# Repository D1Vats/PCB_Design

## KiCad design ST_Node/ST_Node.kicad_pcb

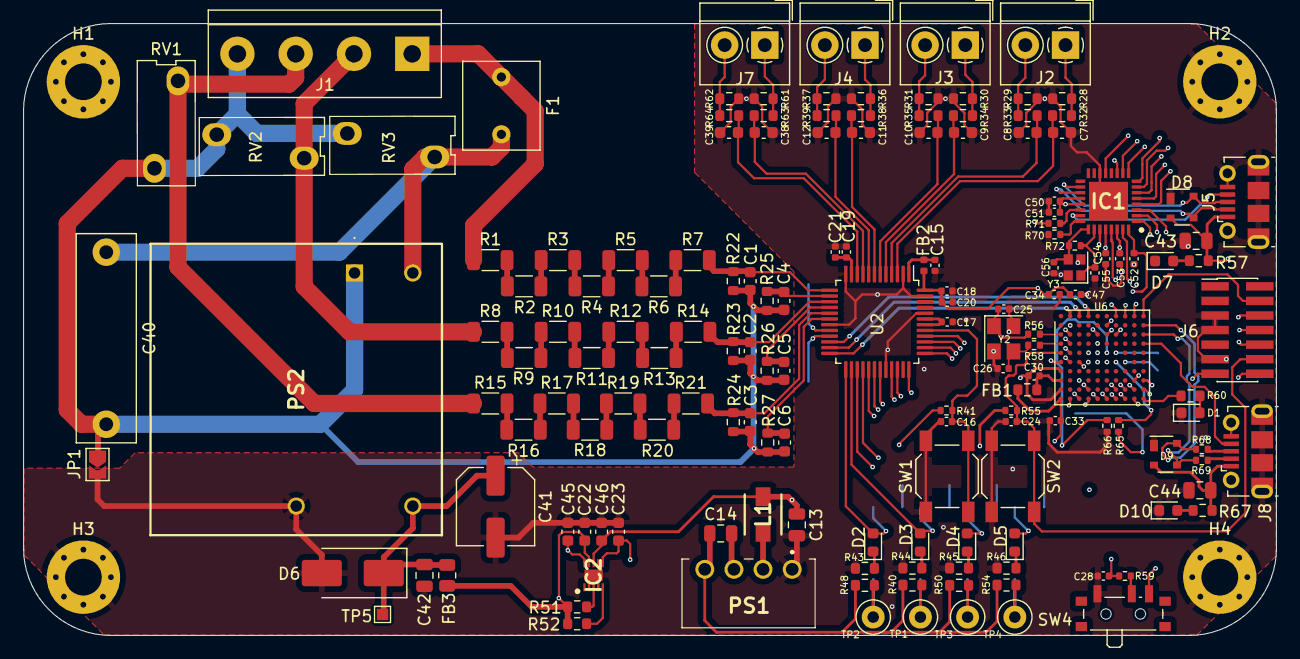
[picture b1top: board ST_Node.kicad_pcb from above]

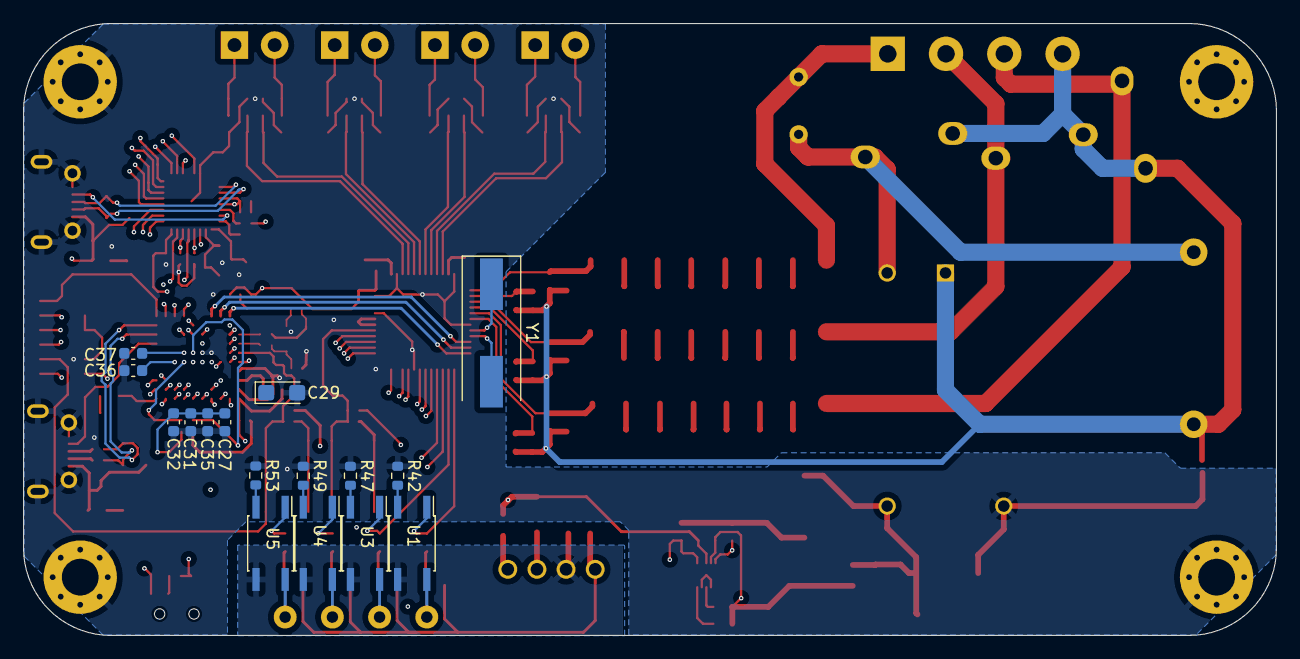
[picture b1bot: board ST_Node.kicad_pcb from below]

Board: 6 copper layers, 109.2 x 53.3 mm, 178 parts (16 on the bottom side), 138 nets.

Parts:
C1, C2, C3, C4, C5, C6, C7, C8, C9, C10, C11, C12, C38, C39: 18nf; C_0603_1608Metric
C13: 4.7uf/16V; C_0805_2012Metric
C14: 10uf/16V; C_0805_2012Metric
C15, C16, C18, C19: 0.1uf; C_0402_1005Metric
C17, C20, C21: 10uf; C_0402_1005Metric
C22, C23: 1uf; C_0603_1608Metric
C24, C28, C33, C34, C47, C50, C51, C52, C53, C54: 100nf; C_0402_1005Metric
C25, C26, C55, C56: 12pf; C_0402_1005Metric
C27, C31, C32: 100nf; C_0603_1608Metric
C29: 1uf; CP_EIA-3216-18_Kemet-A
C30: 10nf; C_0402_1005Metric
C35: 4.7uf; C_0603_1608Metric
C36, C37: 2.2uf; C_0603_1608Metric
C40: 0.1uf/305V; C_Rect_L18.0mm_W5.0mm_P15.00mm_FKS3_FKP3
C41: 100uf/25V; CP_Elec_6.3x7.7
C42: 1uf/50V; C_0805_2012Metric
C43, C44: 4.7nf; C_0805_2012Metric
C45, C46: 10uf; C_0603_1608Metric
D1, D7, D10: Green_LED; LED_0603_1608Metric
D2, D3, D4, D5: LED; LED_0603_1608Metric
D6: SM6T12A; D_SMB_Handsoldering
D8, D9: SP0503BAHT; SOT-143
F1: 2A/300V; C_Rect_L7.5mm_W6.5mm_P5.00mm
FB1: 600@100Mhz; R_0603_1608Metric
FB2: FerriteBead_Small; Fuse_0402_1005Metric
FB3: 120R; R_0805_2012Metric
H1, H2, H3, H4: MountingHole_Pad; MountingHole_3.2mm_M3_Pad_Via
IC1: USB3320C-EZK-TR; QFN50P500X500X100-33N-D
IC2: TLV751180330PDSQR; SON40P200X200X80-11N
J1: 3Phase_Input; TerminalBlock_bornier-4_P5.08mm
J2: CT_Coil_1; TerminalBlock_4Ucon_1x02_P3.50mm_Horizontal
J3: CT_Coil_2; TerminalBlock_4Ucon_1x02_P3.50mm_Horizontal
J4, J7: CT_Coil_3; TerminalBlock_4Ucon_1x02_P3.50mm_Horizontal
J5, J8: USB_B_Micro; USB_Micro-B_Molex-105017-0001
J6: Conn_ST_STDC14; PinHeader_2x07_P1.27mm_Vertical_SMD
JP1: Jumper_2_Open; SolderJumper-2_P1.3mm_Open_TrianglePad1.0x1.5mm
L1: SRP3012CC-6R8M; INDPM3532X120N
PS1: B0303S-1WR2; B0303S1WR2
PS2: RACM06E-05SK_277; RACM06E05SK277
R1, R2, R3, R4, R5, R6, R7, R8, R9, R10, R11, R12, R13, R14, R15, R16, R17, R18, R19, R20, R21: 240k; R_1206_3216Metric
R22, R23, R24, R25, R26, R27, R57, R60, R67: 1k; R_0603_1608Metric
R28, R29, R30, R31, R36, R37, R61, R62: 2R7; R_0603_1608Metric
R32, R33, R34, R35, R38, R39, R63, R64: 1K; R_0603_1608Metric
R40, R42, R43, R44, R45, R46, R47, R48, R49, R50, R53, R54: 510R; R_0603_1608Metric
R41, R55, R59, R65, R66: 10k; R_0402_1005Metric
R51, R52: 100k; R_0603_1608Metric
R56, R58: 0R; R_0402_1005Metric
R68, R69: 22E; R_0402_1005Metric
R70: 8.06k; R_0402_1005Metric
R71: 1k; R_0402_1005Metric
R72: 1M; R_0402_1005Metric
RV1, RV2, RV3: S14K350; DIP-2_81_ELL
SW1, SW2: SW_Push; SW_SPST_SKQG_WithStem
SW4: SW_SPDT; SW_SPDT_PCM12
TP1, TP2, TP3, TP4: TestPoint_Probe; TestPoint_Loop_D1.80mm_Drill1.0mm_Beaded
TP5: TestPoint; TestPoint_Pad_1.0x1.0mm
U1, U3, U4, U5: EL817; SO-4_4.4x3.6mm_P2.54mm
U2: M90E36A; LQFP-48_7x7mm_P0.5mm
U6: STM32F746VGHx; TFBGA-100_8x8mm_Layout10x10_P0.8mm
Y1: 16Mhz; Crystal_SMD_HC49-SD
Y2: 16MHz; Crystal_SMD_3225-4Pin_3.2x2.5mm
Y3: 27Mhz; Crystal_SMD_2016-4Pin_2.0x1.6mm

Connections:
3V3_ISO: C14.1, PS1.4 (+VO), R40.2, R48.2, R50.2, R54.2
AC_IN_1/L: F1.1, J1.1, R1.1
AC_IN_2/L: J1.2, R8.1, RV2.1
AC_IN_3/L: J1.3, R15.1, RV1.1
AC_IN/N: C1.2, C2.2, C3.2, C4.2, C5.2, C6.2, C40.2, J1.4, JP1.1 (A), PS2.1 (VAC_IN_(L)), R22.1, R23.1, R24.1, R25.1, R26.1, R27.1, RV1.2, RV2.2, RV3.2
AVDD: C15.1, FB2.2, U2.1 (AVDD)
BOOT_0: C28.1, R59.2, U6.D5 (BOOT0)
BYPASS_REG: R66.1, U6.E6 (BYPASS_REG)
CF1: D2.2 (A), U1.1, U2.25 (CF1)
CF2: D3.2 (A), U2.26 (CF2), U3.1
CF3: D4.2 (A), U2.27 (CF3), U4.1
CF4: D5.2 (A), U2.28 (CF4), U5.1
CS_M90: U2.37 (CS), U6.H9 (PD10)
Coil_1N: J2.2, R29.1, R33.1
Coil_1P: J2.1, R28.2, R32.1
Coil_2N: J3.2, R31.1, R35.1
Coil_2P: J3.1, R30.2, R34.1
Coil_3N: J4.2, R37.1, R39.1
Coil_3P: J4.1, R36.2, R38.1
Coil_4N: J7.2, R62.1, R64.1
Coil_4P: J7.1, R61.2, R63.1
D+: D8.4 (K), IC1.18 (DP), J5.3 (D+)
D-: D8.3 (K), IC1.19 (DM), J5.2 (D-)
DMA_CTRL: U2.36 (DMA_CTRL), U6.J9 (PD9)
Filter_V_IN: C22.1, C23.1, FB3.2, IC2.6 (IN2), IC2.9 (IN1), R51.1, R52.1
GND: C7.2, C8.1, C9.2, C10.1, C11.2, C12.1, C13.2, C15.2, C16.2, C17.2, C18.2, C19.2, C20.2, C21.2, C22.2, C23.2, C24.2, C25.2, C26.2, C27.2, C28.2, C29.2, C30.2, C31.2, C32.2, C33.2, C34.2, C35.2, C36.2, C37.2, C38.2, C39.1, C41.2, C42.2, C43.2, C44.2, C45.2, C46.2, C47.2, C50.2, C51.2, C52.2, C53.2, C54.2, C55.2, C56.2, D1.1 (K), D6.2 (A2), D8.1 (A), D9.1 (A), D10.1 (K), H2.1, H3.1, H4.1, IC1.14 (REFSEL2), IC1.33 (EP), IC2.2 (GND_1), IC2.4 (GND_2), IC2.11 (EP), J5.5 (GND), J5.6 (Shield), J6.5 (GND), J6.7 (GND), J6.11 (GNDDetect), J8.5 (GND), J8.6 (Shield), JP1.2 (B), PS1.1 (GND), PS2.4 (-VOUT), R28.1, R29.2, R30.1, R31.2, R36.1, R37.2, R42.1, R43.1, R44.1, R45.1, R46.1, R47.1, R49.1, R53.1, R61.1, R62.2, R66.2, R70.2, SW1.1, SW2.1, SW4.1 (A), U2.2 (AGND), U2.12 (AGND), U2.19 (DGND), U2.32 (TEST), U2.44 (DGND), U2.47 (DGND), U6.C2 (VSS), U6.E4 (VSS), U6.E5 (VSS), U6.G1 (VSSA), U6.J1 (VSS), Y2.2, Y2.4, Y3.2, Y3.4
GND_ISO: C14.2, PS1.3 (0V), U1.3, U3.3, U4.3, U5.3
I1N: C8.2, R33.2, U2.4 (I1N)
I1P: C7.1, R32.2, U2.3 (I1P)
I2N: C10.2, R35.2, U2.6 (I2N)
I2P: C9.1, R34.2, U2.5 (I2P)
I3N: C12.2, R39.2, U2.8 (I3N)
I3P: C11.1, R38.2, U2.7 (I3P)
I4N: C39.2, R64.2, U2.10 (I4N)
I4P: C38.1, R63.2, U2.9 (I4P)
ID: IC1.23 (ID), J5.4 (ID)
ID_1: J8.4 (ID), U6.D10 (PA10)
IRQ0: U2.30 (IRQ0), U6.K5 (PE9)
IRQ1: U2.31 (IRQ1), U6.K6 (PE13)
NRST: C24.1, J6.12 (~RST), R55.2, SW2.2, U6.E1 (NRST)
unnamed: C25.1, R56.2, Y2.1
unnamed: C26.1, R58.1, Y2.3
unnamed: D1.2 (A), R60.2
unnamed: D2.1 (K), R43.2
unnamed: D3.1 (K), R44.2
unnamed: D4.1 (K), R45.2
unnamed: D5.1 (K), R46.2
unnamed: D7.2 (A), R57.2
unnamed: D10.2 (A), R67.2
unnamed: IC1.24 (RBIAS), R70.1
unnamed: IC1.22 (VBUS), R71.1
unnamed: IC2.3 (EN1), R51.2
unnamed: IC2.5 (EN2), R52.2
unnamed: J8.3 (D+), R68.1
unnamed: J8.2 (D-), R69.1
unnamed: L1.2, PS1.2 (VIN)
unnamed: C40.1, F1.2, PS2.2 (VAC_IN_(N)), RV3.1
unnamed: R1.2, R2.1
unnamed: R2.2, R3.1
unnamed: R3.2, R4.1
unnamed: R4.2, R5.1
unnamed: R5.2, R6.1
unnamed: R6.2, R7.1
unnamed: R8.2, R9.1
unnamed: R9.2, R10.1
unnamed: R10.2, R11.1
unnamed: R11.2, R12.1
unnamed: R12.2, R13.1
unnamed: R13.2, R14.1
unnamed: R15.2, R16.1
unnamed: R16.2, R17.1
unnamed: R17.2, R18.1
unnamed: R18.2, R19.1
unnamed: R19.2, R20.1
unnamed: R20.2, R21.1
unnamed: R40.1, TP1.1, U3.4
unnamed: R42.2, U1.2
unnamed: R47.2, U3.2
unnamed: R48.1, TP2.1, U1.4
unnamed: R49.2, U4.2
unnamed: R50.1, TP3.1, U4.4
unnamed: R53.2, U5.2
unnamed: R54.1, TP4.1, U5.4
unnamed: R59.1, SW4.2 (B)
unnamed: C36.1, U6.F8 (VCAP_1)
unnamed: C37.1, U6.E7 (VCAP_2)
OSCI: U2.20 (OSCI), Y1.1
OSCO: U2.21 (OSCO), Y1.2
OSC_IN: R56.1, U6.C1 (PH0)
OSC_OUT: R58.2, U6.D1 (PH1)
PDR_ON: R65.2, U6.F7 (PDR_ON)
PM0: U2.33 (PM0), U6.K9 (PD8)
PM1: U2.34 (PM1), U6.J10 (PD13)
REFCLK: C55.1, IC1.26 (REFCLK), R72.1, Y3.1
Reset_M90: C16.1, R41.2, SW1.2, U2.41 (RESET)
SCLK_M90: U2.38 (SCLK), U6.C7 (PD3)
SDI_M90: U2.40 (SDI), U6.F2 (PC1)
SDO_M90: U2.39 (SDO), U6.H10 (PB14)
SYS_JTDI: J6.10 (JTDI/NC), U6.A8 (PA15)
SYS_SWCLK: J6.6 (JCLK/SWCLK), U6.A9 (PA14)
SYS_SWDIO: J6.4 (JTMS/SWDIO), U6.A10 (PA13)
SYS_SWO: J6.8 (JTDO/SWO), U6.A7 (PB3)
Test_LED: R60.1, U6.K10 (PD12)
USART2_RX: J6.13 (VCP_RX), U6.C6 (PD6)
USART2_TX: J6.14 (VCP_TX), U6.B6 (PD5)
USB3320_CK: IC1.1 (CLKOUT), U6.H3 (PA5)
USB3320_DIR: IC1.31 (DIR), U6.E2 (PC2)
USB3320_NXT: IC1.2 (NXT), U6.F3 (PC3)
USB3320_STP: IC1.29 (STP), U6.F1 (PC0)
USB_D+: D9.4 (K), R68.2, U6.B10 (PA12)
USB_D-: D9.3 (K), R69.2, U6.C10 (PA11)
USB_DATA_0: IC1.3 (DATA0), U6.K2 (PA3)
USB_DATA_1: IC1.4 (DATA1), U6.J4 (PB0)
USB_DATA_2: IC1.5 (DATA2), U6.K4 (PB1)
USB_DATA_3: IC1.6 (DATA3), U6.J7 (PB10)
USB_DATA_4: IC1.7 (DATA4), U6.K7 (PB11)
USB_DATA_5: IC1.9 (DATA5), U6.K8 (PB12)
USB_DATA_6: IC1.10 (DATA6), U6.J8 (PB13)
USB_DATA_7: IC1.13 (DATA7), U6.C5 (PB5)
USB_VDD33: C13.1, C18.1, C20.1, C27.1, C31.1, C32.1, C33.1, C34.1, C35.1, C46.1, C47.1, C50.1, C51.1, FB1.1, FB2.1, IC1.20 (VDD33), IC1.21 (VBAT), IC2.8 (OUT2), L1.1, R41.1, R55.1, R65.1, SW4.3 (C), U2.48 (DVDD), U6.B2 (VBAT), U6.D2 (VDD), U6.F4 (VDD), U6.F5 (VDD), U6.F6 (VDDUSB), U6.K1 (VDD)
USB_VDDIO: C45.1, C52.1, C53.1, C54.1, IC1.8 (REFSEL0), IC1.11 (REFSEL1), IC1.28 (VDD18_1), IC1.30 (VDD18_2), IC1.32 (VDDIO), IC2.10 (OUT1)
V1N: C4.1, R25.2, U2.14 (V1N)
V1P: C1.1, R7.2, R22.2, U2.13 (V1P)
V2N: C5.1, R26.2, U2.16 (V2N)
V2P: C2.1, R14.2, R23.2, U2.15 (V2P)
V3N: C6.1, R27.2, U2.18 (V3N)
V3P: C3.1, R21.2, R24.2, U2.17 (V3P)
VBUS: C43.1, D8.2 (K), J5.1 (VBUS), R57.1, R71.2
VBUS_FS: C44.1, D9.2 (K), J8.1 (VBUS), R67.1
VDAA: C29.1, C30.1, FB1.2, U6.H1 (VDDA)
VDD18: C17.1, U2.42 (VDD18), U2.43 (VDD18)
VREF: C19.1, C21.1, U2.11 (Vref)
V_IN: C41.1, C42.1, D6.1 (A1), FB3.1, PS2.5 (+VOUT), TP5.1
WarnOut: U2.29 (WarnOut), U6.K3 (PA7)
XO: C56.1, IC1.25 (XO), R72.2, Y3.3
ZX_0: U2.22 (ZX0), U6.A4 (PB9)
ZX_1: U2.23 (ZX1), U6.A3 (PE2)
ZX_2: U2.24 (ZX2), U6.A2 (PC13)

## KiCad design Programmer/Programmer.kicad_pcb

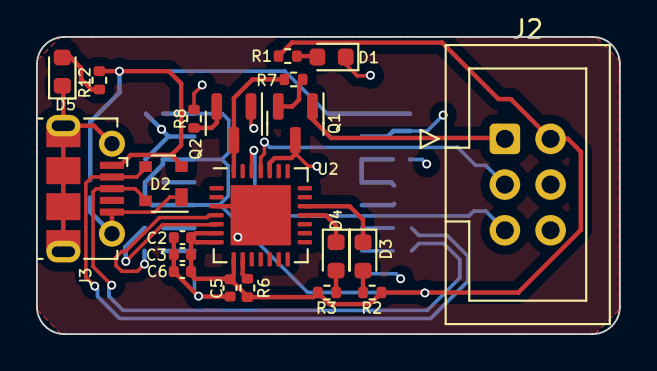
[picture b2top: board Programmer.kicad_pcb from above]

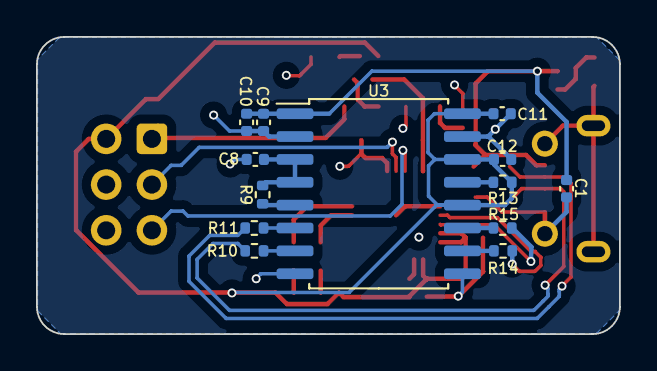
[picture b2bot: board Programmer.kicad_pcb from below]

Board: 4 copper layers, 32.4 x 16.5 mm, 34 parts (13 on the bottom side), 30 nets.

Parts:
C1, C3, C6, C8, C9, C11, C12: 0.1uf; C_0402_1005Metric
C2, C5: 4.7uf; C_0402_1005Metric
C10: 10uf; C_0402_1005Metric
D1, D3, D4, D5: LED; LED_0603_1608Metric
D2: SP0503BAHT; SOT-143
J2: Conn_02x03_Odd_Even; IDC-Header_2x03_P2.54mm_Vertical
J3: USB_B_Micro; USB_Micro-B_Molex-105017-0001
Q1, Q2: SS8050; SOT-23
R1, R2, R3, R12: 2.2k; R_0402_1005Metric
R6: 1K; R_0402_1005Metric
R7, R8: 10k; R_0402_1005Metric
R9, R13: 0R; R_0402_1005Metric
R10, R11, R14, R15: 24E; R_0402_1005Metric
U2: CP2102N-Axx-xQFN28; QFN-28-1EP_5x5mm_P0.5mm_EP3.35x3.35mm
U3: ADUM4160; SOIC-16W_7.5x10.3mm_P1.27mm

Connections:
CP_D+: R14.1, U2.4 (D+)
CP_D-: R15.1, U2.5 (D-)
D+: D2.4 (K), J3.3 (D+), R10.2
D-: D2.3 (K), J3.2 (D-), R11.2
DTR: Q2.3 (E), R7.1, U2.28 (~DTR)
ESP_EN: J2.1, Q1.1 (C)
ESP_IO0_B: J2.6, Q2.1 (C)
GND: C2.2, C3.2, C5.2, C6.2, C11.2, C12.2, D1.1 (K), J2.4, U2.3 (GND), U2.29 (GND), U3.9 (GND2), U3.15 (GND2)
GND_USB: C1.2, C8.2, C9.1, C10.1, D2.1 (A), D5.1 (K), J3.5 (GND), J3.6 (Shield), U3.2 (GND1), U3.8 (GND1)
unnamed: D1.2 (A), R1.1
unnamed: D3.2 (A), R2.1
unnamed: D4.2 (A), R3.1
unnamed: D5.2 (A), R12.2
unnamed: Q1.2 (B), R7.2
unnamed: Q2.2 (B), R8.2
unnamed: R6.2, U2.9 (~RST)
unnamed: R14.2, U3.10 (DD+)
unnamed: R15.2, U3.11 (DD-)
RTS: Q1.3 (E), R8.1, U2.24 (~RTS)
RXD: J2.3, U2.25 (RXD)
RXT: D4.1 (K), U2.18 (~RXT/GPIO.1)
SPD: R13.2, U3.13 (SPD)
SPU: R9.2, U3.5 (SPU)
TXD: J2.5, U2.26 (TXD)
TXT: D3.1 (K), U2.19 (~TXT/GPIO.0)
UD+: R10.1, U3.7 (UD+)
UD-: R11.1, U3.6 (UD-)
VDD1: C8.1, R9.1, U3.3 (VDD1), U3.4 (PDEN)
VOUT: C2.1, C3.1, C5.1, C6.1, C11.1, C12.1, J2.2, R1.2, R2.2, R3.2, R6.1, R13.1, U2.6 (VDD), U2.7 (VREGIN), U2.8 (VBUS), U3.12 (PIN), U3.14 (VDD2), U3.16 (VBUS2)
V_USB: C1.1, C9.2, C10.2, D2.2 (K), J3.1 (VBUS), R12.1, U3.1 (VBUS1)

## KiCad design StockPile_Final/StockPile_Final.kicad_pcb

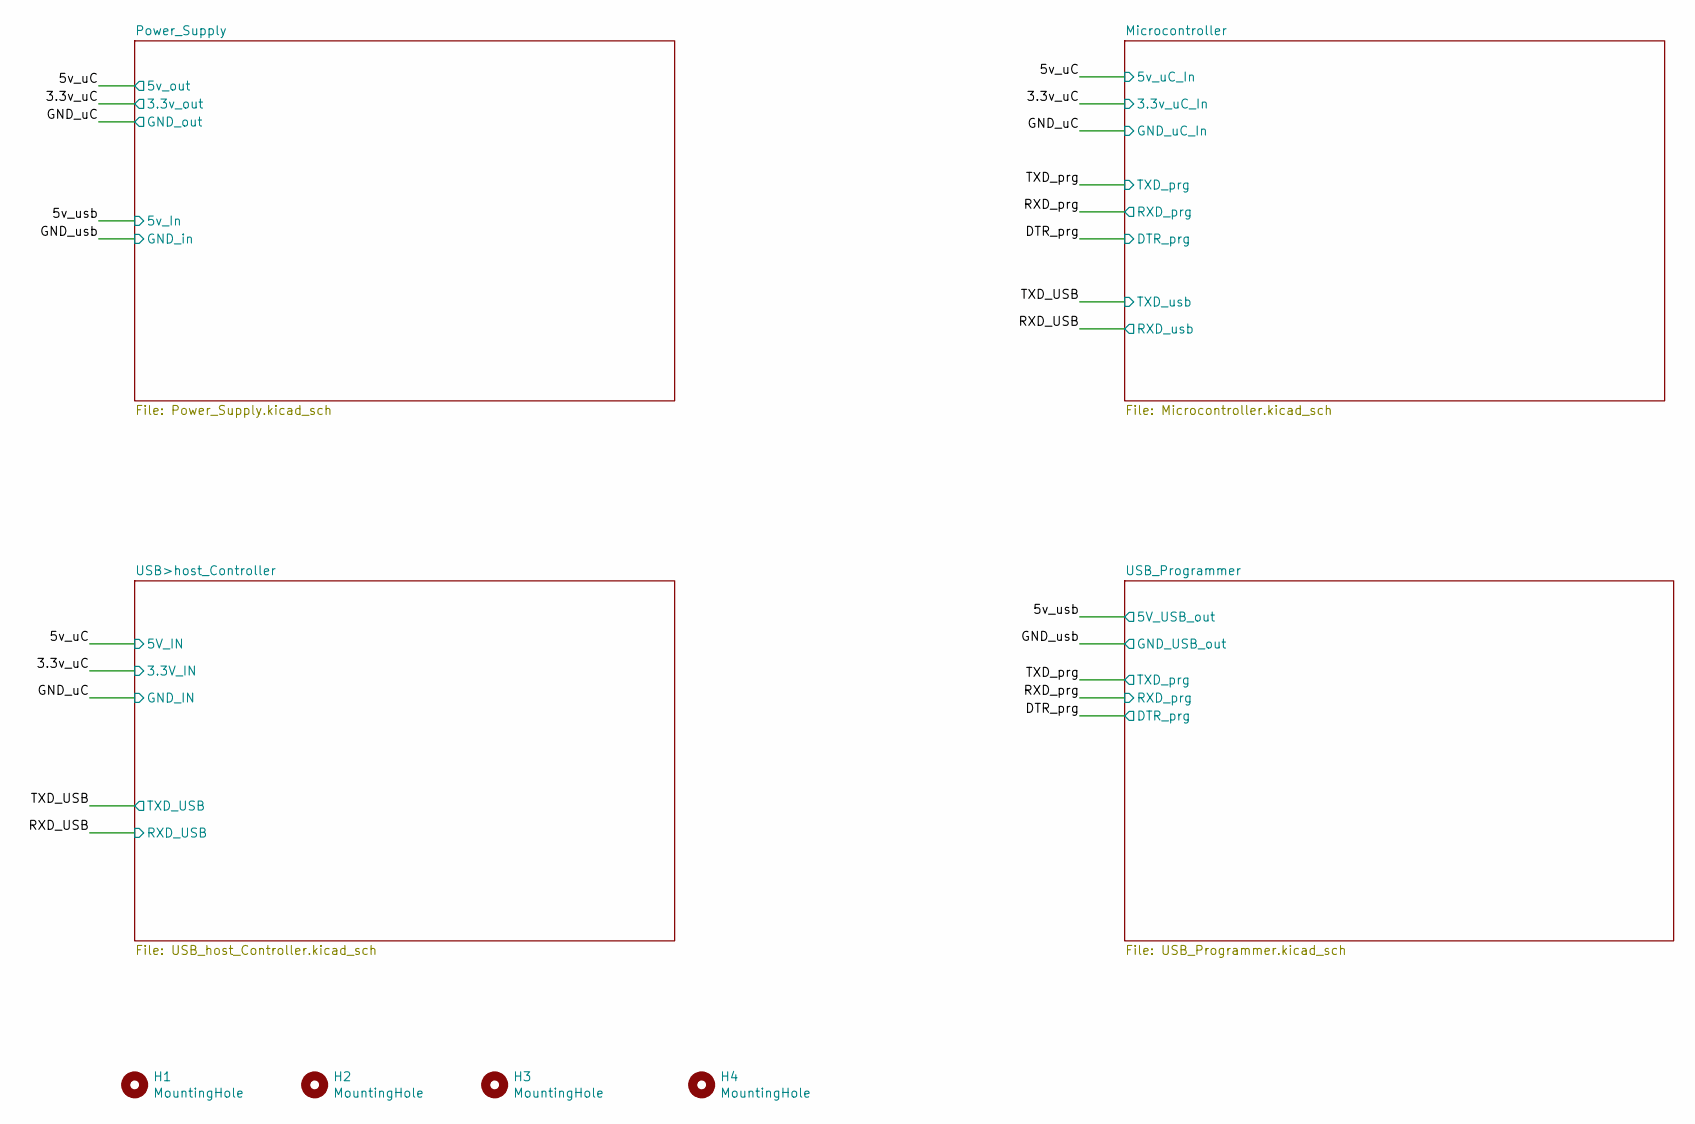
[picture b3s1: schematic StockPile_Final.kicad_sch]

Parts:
H1, H2, H3, H4: MountingHole; MountingHole_3.2mm_M3

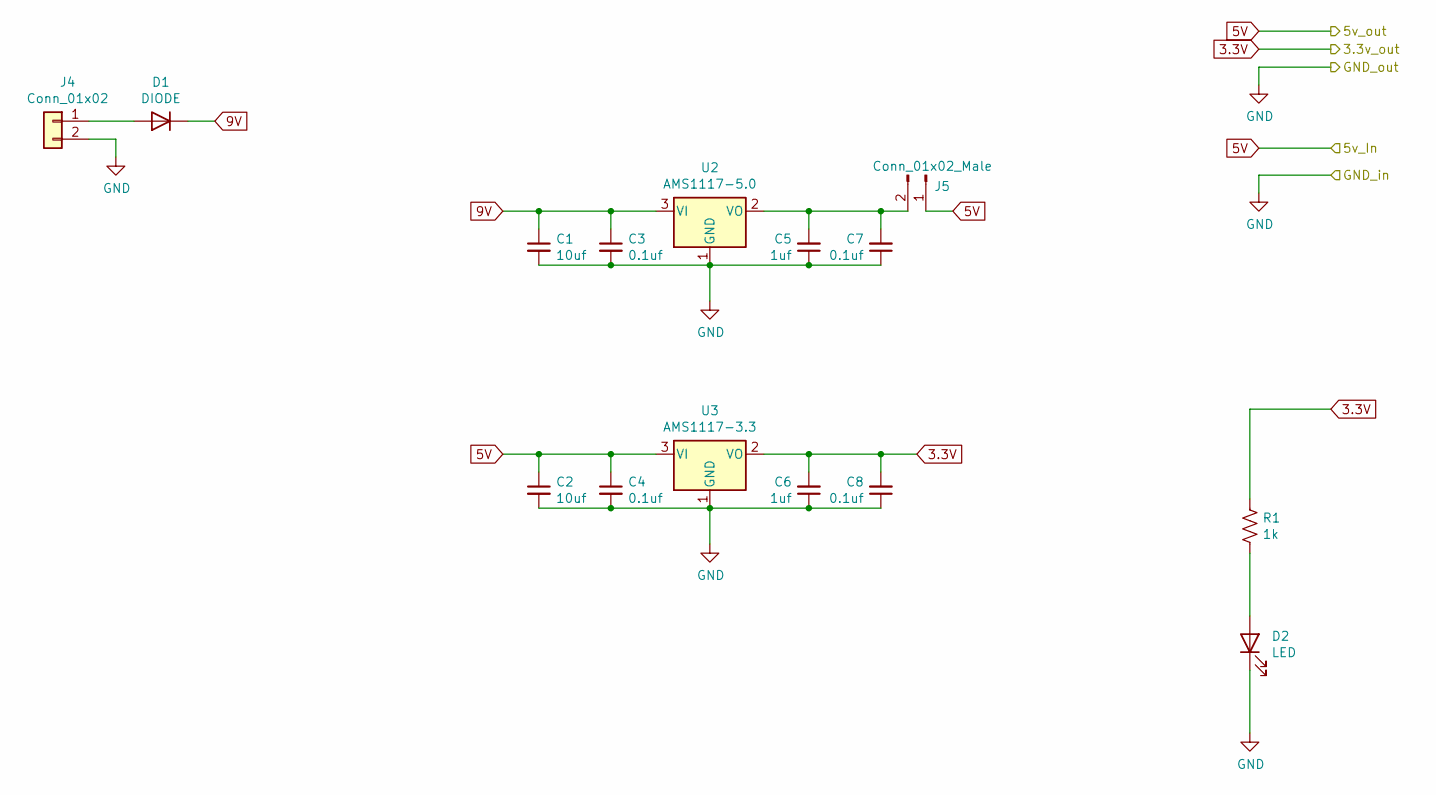
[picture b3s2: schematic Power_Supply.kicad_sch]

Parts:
C1, C2: 10uf; C_0805_2012Metric
C3, C4, C7, C8: 0.1uf; C_0805_2012Metric
C5, C6: 1uf; C_0805_2012Metric
D1: DIODE; D_SOD-323_HandSoldering
D2: LED; LED_0805_2012Metric
J4: Conn_01x02; JST_XH_B2B-XH-AM_1x02_P2.50mm_Vertical
J5: Conn_01x02_Male; PinSocket_1x02_P2.54mm_Vertical
R1: 1k; R_0805_2012Metric
U2: AMS1117-5.0; SOT-223-3_TabPin2
U3: AMS1117-3.3; SOT-223-3_TabPin2

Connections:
3.3V: C6.2, C8.2, R1.1, U3.2 (VO); also elsewhere on the board
5V: C2.1, C4.1, J5.1, U3.3 (VI); also elsewhere on the board
9V: C1.1, C3.1, D1.2 (K), U2.3 (VI)
GND_USB: C1.2, C2.2, C3.2, C4.2, C5.1, C6.1, C7.1, C8.1, D2.1 (K), J4.2, U2.1 (GND), U3.1 (GND); also elsewhere on the board
unnamed: C5.2, C7.2, J5.2, U2.2 (VO)
unnamed: D1.1 (A), J4.1
unnamed: D2.2 (A), R1.2

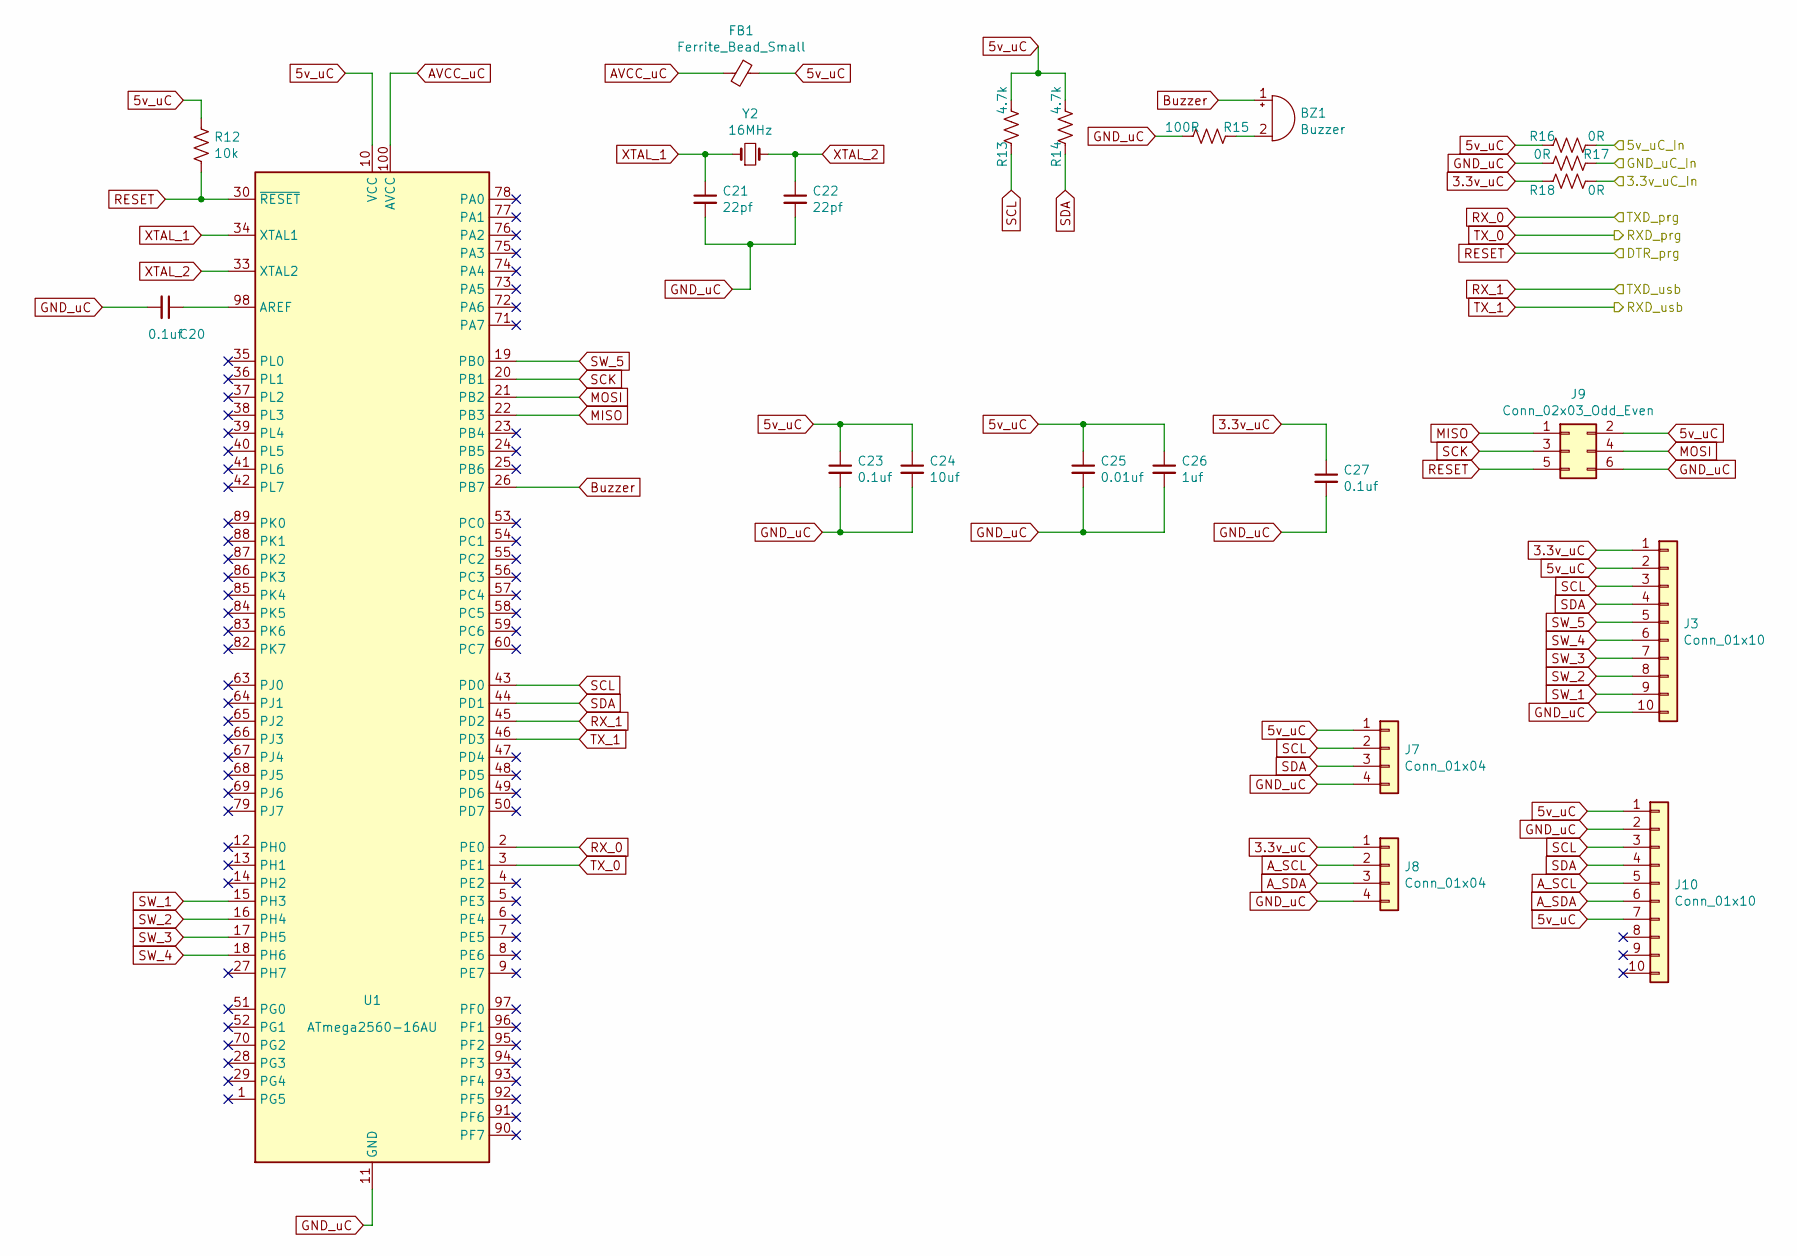
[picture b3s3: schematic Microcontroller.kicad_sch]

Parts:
BZ1: Buzzer; Buzzer_12x9.5RM7.6
C20, C23, C27: 0.1uf; C_0805_2012Metric
C21, C22: 22pf; C_0805_2012Metric
C24: 10uf; C_0805_2012Metric
C25: 0.01uf; C_0805_2012Metric
C26: 1uf; C_0805_2012Metric
FB1: Ferrite_Bead_Small; L_0805_2012Metric
J3, J10: Conn_01x10; JST_XH_B10B-XH-AM_1x10_P2.50mm_Vertical
J7, J8: Conn_01x04; PinSocket_1x04_P2.54mm_Horizontal
J9: Conn_02x03_Odd_Even; PinSocket_2x03_P2.54mm_Vertical
R12: 10k; R_0805_2012Metric
R13, R14: 4.7k; R_0805_2012Metric
R15: 100R; R_0805_2012Metric
R16, R17, R18: 0R; R_0805_2012Metric
U1: ATmega2560-16AU; TQFP-100_14x14mm_P0.5mm
Y2: 16MHz; Crystal_HC49-4H_Vertical

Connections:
3.3V: R18.1; also elsewhere on the board
3.3v_uC: C27.1, J3.1, J8.1, R18.2
5V: R16.1; also elsewhere on the board
5v_uC: C23.1, C24.1, C25.1, C26.1, FB1.1, J3.2, J7.1, J9.2, J10.1, J10.7, R12.1, R13.1, R14.2, R16.2, U1.10 (VCC), U1.31 (VCC), U1.61 (VCC), U1.80 (VCC)
AVCC_uC: FB1.2, U1.100 (AVCC)
A_SCL: J8.2, J10.5
A_SDA: J8.3, J10.6
Buzzer: BZ1.1 (-), U1.26 (PB7)
DTR_prg: J9.5, R12.2, U1.30 (~RESET); also elsewhere on the board
GND_USB: R17.2; also elsewhere on the board
GND_uC: C20.2, C21.2, C22.2, C23.2, C24.2, C25.2, C26.2, C27.2, J3.10, J7.4, J8.4, J9.6, J10.2, R15.1, R17.1, U1.11 (GND), U1.32 (GND), U1.62 (GND), U1.81 (GND), U1.99 (GND)
MISO: J9.1, U1.22 (PB3)
MOSI: J9.4, U1.21 (PB2)
unnamed: BZ1.2 (+), R15.2
unnamed: C20.1, U1.98 (AREF)
RXD_prg: U1.3 (PE1); also elsewhere on the board
RXD_usb: U1.46 (PD3); also elsewhere on the board
RX_0: U1.2 (PE0); also elsewhere on the board
RX_1: U1.45 (PD2); also elsewhere on the board
SCK: J9.3, U1.20 (PB1)
SCL: J3.3, J7.2, J10.3, R13.2, U1.43 (PD0)
SDA: J3.4, J7.3, J10.4, R14.1, U1.44 (PD1)
SW_1: J3.9, U1.15 (PH3)
SW_2: J3.8, U1.16 (PH4)
SW_3: J3.7, U1.17 (PH5)
SW_4: J3.6, U1.18 (PH6)
SW_5: J3.5, U1.19 (PB0)
XTAL_1: C21.1, U1.34 (XTAL1), Y2.1
XTAL_2: C22.1, U1.33 (XTAL2), Y2.2

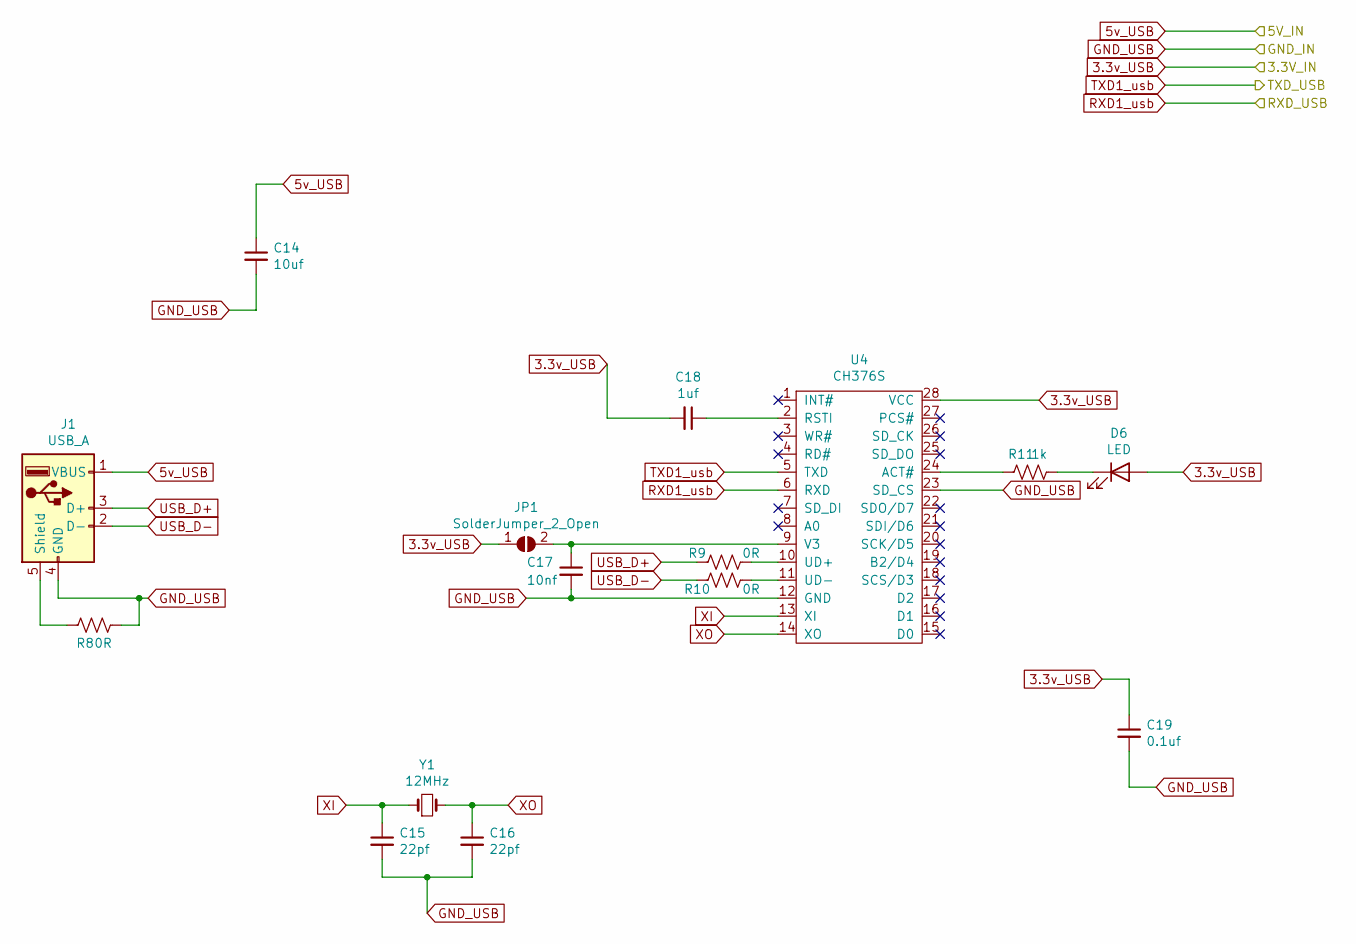
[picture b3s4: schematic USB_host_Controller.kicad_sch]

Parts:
C14: 10uf; C_0805_2012Metric
C15, C16: 22pf; C_0805_2012Metric
C17: 10nf; C_0805_2012Metric
C18: 1uf; C_0805_2012Metric
C19: 0.1uf; C_0805_2012Metric
D6: LED; LED_0805_2012Metric
J1: USB_A; USB_A_Molex_67643_Horizontal
JP1: SolderJumper_2_Open; SolderJumper-2_P1.3mm_Open_RoundedPad1.0x1.5mm
R8, R9, R10: 0R; R_0805_2012Metric
R11: 1k; R_0805_2012Metric
U4: CH376S; SOIC-28W_7.5x17.9mm_P1.27mm
Y1: 12MHz; Crystal_HC49-4H_Vertical

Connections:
3.3V: C18.2, C19.1, D6.2 (A), JP1.1 (A), U4.28 (VCC); also elsewhere on the board
5V: C14.1, J1.1 (VBUS); also elsewhere on the board
GND_USB: C14.2, C15.2, C16.2, C17.2, C19.2, J1.4 (GND), R8.1, U4.12 (GND), U4.23 (SD_CS); also elsewhere on the board
unnamed: C17.1, JP1.2 (B), U4.9 (V3)
unnamed: C18.1, U4.2 (RSTI)
unnamed: D6.1 (K), R11.1
unnamed: J1.5 (Shield), R8.2
unnamed: R9.1, U4.10 (UD+)
unnamed: R10.1, U4.11 (UD-)
unnamed: R11.2, U4.24 (ACT#)
RXD_usb: U4.6 (RXD); also elsewhere on the board
RX_1: U4.5 (TXD); also elsewhere on the board
USB_D+: J1.3 (D+), R9.2
USB_D-: J1.2 (D-), R10.2
XI: C15.1, U4.13 (XI), Y1.1
XO: C16.1, U4.14 (XO), Y1.2

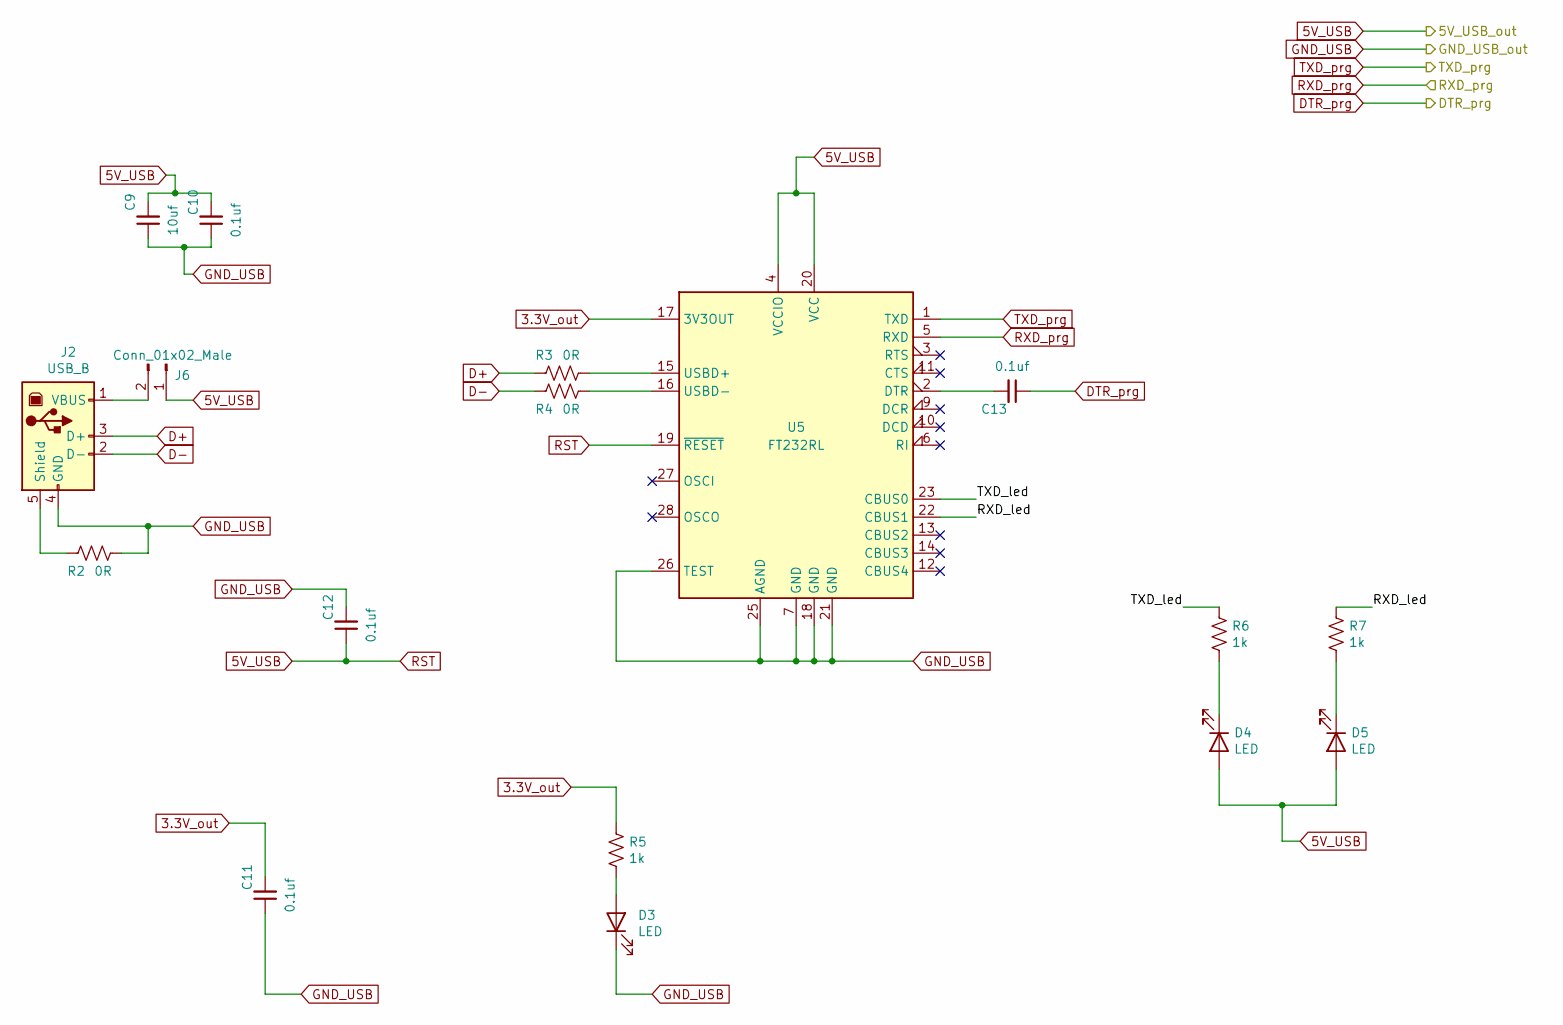
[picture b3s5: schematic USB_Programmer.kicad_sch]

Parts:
C9: 10uf; C_0805_2012Metric
C10, C11, C12, C13: 0.1uf; C_0805_2012Metric
D3, D4, D5: LED; LED_0805_2012Metric
J2: USB_B; USB_B_OST_USB-B1HSxx_Horizontal
J6: Conn_01x02_Male; PinSocket_1x02_P2.54mm_Vertical
R2, R3, R4: 0R; R_0805_2012Metric
R5, R6, R7: 1k; R_0805_2012Metric
U5: FT232RL; SSOP-28_5.3x10.2mm_P0.65mm

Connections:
3.3V_out: C11.2, R5.1, U5.17 (3V3OUT)
5V: C9.2, C10.2, C12.1, D4.2 (A), D5.2 (A), J6.1, U5.4 (VCCIO), U5.19 (~RESET), U5.20 (VCC); also elsewhere on the board
/USB_Programmer/RXD_led: R7.1, U5.22 (CBUS1)
/USB_Programmer/TXD_led: R6.1, U5.23 (CBUS0)
D+: J2.3 (D+), R3.2
D-: J2.2 (D-), R4.2
DTR_prg: C13.1; also elsewhere on the board
GND_USB: C9.1, C10.1, C11.1, C12.2, D3.1 (K), J2.4 (GND), R2.1, U5.7 (GND), U5.18 (GND), U5.21 (GND), U5.25 (AGND), U5.26 (TEST); also elsewhere on the board
unnamed: C13.2, U5.2 (DTR)
unnamed: D3.2 (A), R5.2
unnamed: D4.1 (K), R6.2
unnamed: D5.1 (K), R7.2
unnamed: J2.1 (VBUS), J6.2
unnamed: J2.5 (Shield), R2.2
unnamed: R3.1, U5.15 (USBD+)
unnamed: R4.1, U5.16 (USBD-)
RXD_prg: U5.5 (RXD); also elsewhere on the board
RX_0: U5.1 (TXD); also elsewhere on the board

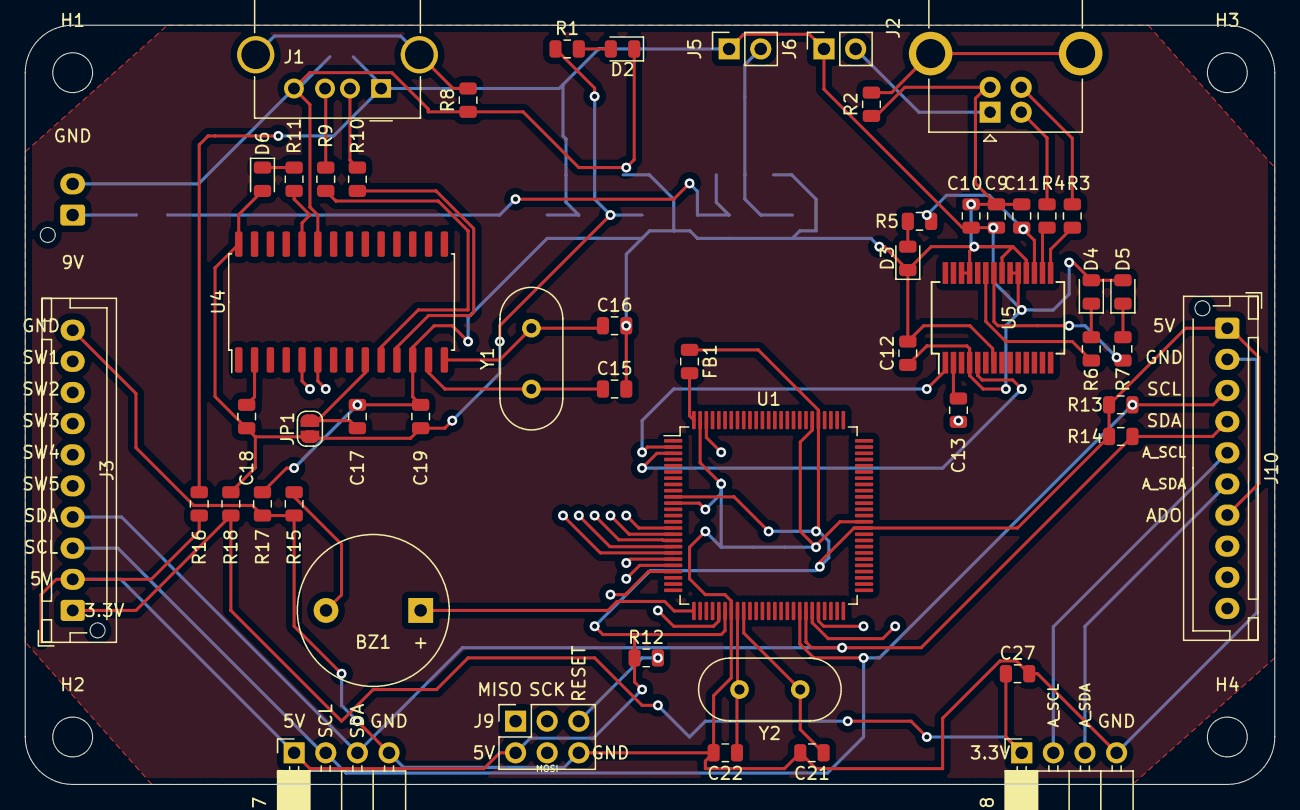
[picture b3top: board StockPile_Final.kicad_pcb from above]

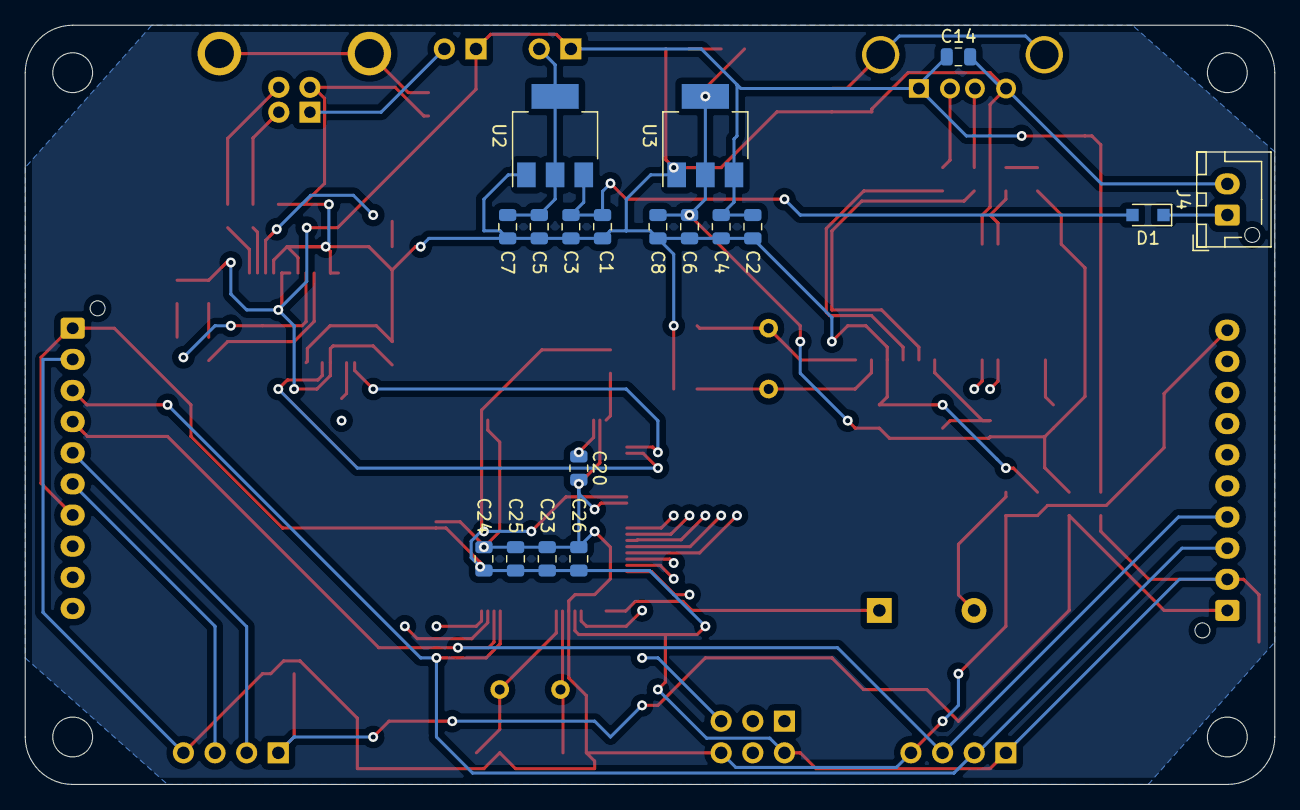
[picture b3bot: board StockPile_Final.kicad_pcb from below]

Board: 4 copper layers, 100.3 x 61.0 mm, 75 parts (18 on the bottom side), 57 nets.
